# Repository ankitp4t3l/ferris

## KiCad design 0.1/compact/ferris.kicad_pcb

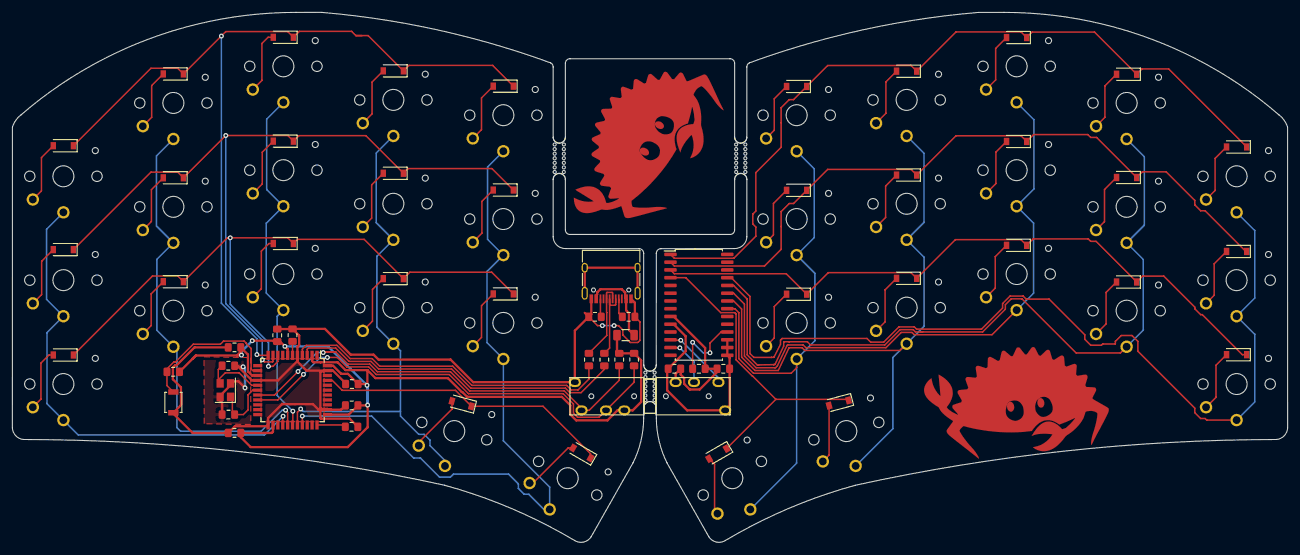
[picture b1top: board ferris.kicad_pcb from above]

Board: 2 copper layers, 208.7 x 86.7 mm, 98 parts (0 on the bottom side), 73 nets.

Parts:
C1, C2: 22p; C_0805_2012Metric_Pad1.15x1.40mm_HandSolder
C3, C4, C5, C6, C9, C10: 0.1u; C_0805_2012Metric_Pad1.15x1.40mm_HandSolder
C7: 4.7u; C_0805_2012Metric_Pad1.15x1.40mm_HandSolder
C8: 1u; C_0805_2012Metric_Pad1.15x1.40mm_HandSolder
D0_0, D0_1, D0_2, D0_3, D0_4, D0_5, D0_6, D0_7, D0_8, D0_9, D1_0, D1_1, D1_2, D1_3, D1_4, D1_5, D1_6, D1_7, D1_8, D1_9, D2_0, D2_1, D2_2, D2_3, D2_4, D2_5, D2_6, D2_7, D2_8, D2_9, D3_3, D3_4, D3_5, D3_6: D; D_SOD-123
F1: 500mA; Fuse_1206_3216Metric
J1: USB C; USB_C_Receptacle_HRO_TYPE-C-31-M-12
Jack0, Jack1: TRRS; TRRS-PJ-320A
K0_0, K0_1, K0_2, K0_3, K0_4, K0_5, K0_6, K0_7, K0_8, K0_9, K1_0, K1_1, K1_2, K1_3, K1_4, K1_5, K1_6, K1_7, K1_8, K1_9, K2_0, K2_1, K2_2, K2_3, K2_4, K2_5, K2_6, K2_7, K2_8, K2_9, K3_3, K3_4, K3_5, K3_6: KEYSW; Choc_PG1350_Choc_Spacing_with_jlcpb_safe_pad_clearance
R1, R2, R9: 10k; R_0805_2012Metric_Pad1.15x1.40mm_HandSolder
R3, R4: 22; R_0805_2012Metric_Pad1.15x1.40mm_HandSolder
R5, R6: 5.1K; R_0805_2012Metric_Pad1.15x1.40mm_HandSolder
R7, R8: 4.7k; R_0805_2012Metric_Pad1.15x1.40mm_HandSolder
SW1: SW_PUSH; SW_SPST_B3U-1000P
U1: ATmega32U4-AU; TQFP-44_10x10mm_P0.8mm
U2: MCP23017_SO; SOIC-28W_7.5x17.9mm_P1.27mm
Y1: Crystal; Crystal_SMD_3225-4Pin_3.2x2.5mm
mouse-bite-5mm-slot, mouse-bite-5mm-slot#2, mouse-bite-5mm-slot#3: VAL**; mouse-bite-5mm-slot

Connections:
+5V: C3.1, C4.1, C5.1, C6.1, C7.1, F1.1, Jack0.R2, R1.2, R7.2, R8.1, U1.2, U1.7, U1.14, U1.24, U1.34, U1.44
/D+: R4.1, U1.4
/D-: R3.1, U1.3
/col0: K0_0.1, K1_0.1, K2_0.1, U1.26
/col1: K0_1.1, K1_1.1, K2_1.1, U1.27
/col2: K0_2.1, K1_2.1, K2_2.1, U1.28
/col3: K0_3.1, K1_3.1, K2_3.1, K3_3.1, U1.29
/col4: K0_4.1, K1_4.1, K2_4.1, K3_4.1, U1.30
/col5: K0_5.1, K1_5.1, K2_5.1, K3_5.1, U2.21
/col6: K0_6.1, K1_6.1, K2_6.1, K3_6.1, U2.22
/col7: K0_7.1, K1_7.1, K2_7.1, U2.23
/col8: K0_8.1, K1_8.1, K2_8.1, U2.24
/col9: K0_9.1, K1_9.1, K2_9.1, U2.25
/row0,0: D0_0.1, D0_1.1, D0_2.1, D0_3.1, D0_4.1, U1.11
/row0,1: D1_0.1, D1_1.1, D1_2.1, D1_3.1, D1_4.1, U1.10
/row0,2: D2_0.1, D2_1.1, D2_2.1, D2_3.1, D2_4.1, U1.9
/row0,3: D3_3.1, D3_4.1, U1.41
/row1,0: D0_5.1, D0_6.1, D0_7.1, D0_8.1, D0_9.1, U2.1
/row1,1: D1_5.1, D1_6.1, D1_7.1, D1_8.1, D1_9.1, U2.2
/row1,2: D2_5.1, D2_6.1, D2_7.1, D2_8.1, D2_9.1, U2.3
/row1,3: D3_5.1, D3_6.1, U2.4
GND: C1.2, C2.1, C3.2, C4.2, C5.2, C6.2, C7.2, C8.2, J1.A1, J1.A12, J1.B1, J1.B12, Jack0.S, R2.1, R5.1, R6.1, SW1.1, U1.5, U1.15, U1.23, U1.35, U1.43, Y1.2, Y1.4
unnamed: C1.1, U1.17, Y1.1
unnamed: C2.2, U1.16, Y1.3
unnamed: C8.1, U1.6
unnamed: D0_0.2, K0_0.2
unnamed: D0_1.2, K0_1.2
unnamed: D0_2.2, K0_2.2
unnamed: D0_3.2, K0_3.2
unnamed: D0_4.2, K0_4.2
unnamed: D0_5.2, K0_5.2
unnamed: D0_6.2, K0_6.2
unnamed: D0_7.2, K0_7.2
unnamed: D0_8.2, K0_8.2
unnamed: D0_9.2, K0_9.2
unnamed: D1_0.2, K1_0.2
unnamed: D1_1.2, K1_1.2
unnamed: D1_2.2, K1_2.2
unnamed: D1_3.2, K1_3.2
unnamed: D1_4.2, K1_4.2
unnamed: D1_5.2, K1_5.2
unnamed: D1_6.2, K1_6.2
unnamed: D1_7.2, K1_7.2
unnamed: D1_8.2, K1_8.2
unnamed: D1_9.2, K1_9.2
unnamed: D2_0.2, K2_0.2
unnamed: D2_1.2, K2_1.2
unnamed: D2_2.2, K2_2.2
unnamed: D2_3.2, K2_3.2
unnamed: D2_4.2, K2_4.2
unnamed: D2_5.2, K2_5.2
unnamed: D2_6.2, K2_6.2
unnamed: D2_7.2, K2_7.2
unnamed: D2_8.2, K2_8.2
unnamed: D2_9.2, K2_9.2
unnamed: D3_3.2, K3_3.2
unnamed: D3_4.2, K3_4.2
unnamed: D3_5.2, K3_5.2
unnamed: D3_6.2, K3_6.2
unnamed: J1.A5, R5.2
unnamed: J1.A6, J1.B6, R4.2
unnamed: J1.A7, J1.B7, R3.2
unnamed: J1.B5, R6.2
unnamed: Jack0.R1, R8.2, U1.19
unnamed: Jack0.T, R7.1, U1.18
unnamed: Jack1.R1, U2.13
unnamed: Jack1.T, U2.12
unnamed: R1.1, SW1.2, U1.13
unnamed: R2.2, U1.33
unnamed: R9.1, U2.18
VCC: F1.2, J1.A4, J1.A9, J1.B4, J1.B9
VDD: C9.2, C10.2, Jack1.R2, R9.2, U2.9
VSS: C9.1, C10.1, Jack1.S, U2.10, U2.15, U2.16, U2.17

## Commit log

2021-09-26 Point footprints submodule to my fork.
2021-09-26 Update submodule ref to point to commit with 5mm tab.
2021-09-26 Make all mouse bites 5mm.
2021-09-27 Make the shebang line compatible with more envs.
    Also add some debugging info to confirm the run-as USER is correct.
2021-09-27 Add JLCPCB order number placeholder.
    Also, make the text on the scrap panel concise.
2021-09-30 Hide all non copper layers.
2021-09-30 Temporarily increase solder mask clearance in order to move traces.
    The solder mask clearance should be set back to 0.05mm after the traces have
    been moved.
2021-09-30 Revert "Temporarily increase solder mask clearance in order to move traces."
    This reverts commit 0fd1c5d82cd2eb1b42baabec2bdd6d8ffa0e2c2a.
2021-09-30 Enable solder mask layers to avoid creating a trace in solder mask clearance.
2021-09-30 Increase pad clearance to 0.7mm.
    Error margins:
    0.2mm NPTH means the hole might be 0.1mm too big around the center.
    0.2mm placement of the hole left or right of where I want it.
    0.254mm is required from NPTH to track
    0.33m is required from PTH to track (we will use this value since it is the greater of NPTH and PTH)
    So, that means, from the edge of the hole to the trace needs to be 0.33mm+0.2mm+0.1mm = 0.63mm
2021-09-30 Modify the switch footprint to add pad clearance.
2021-10-03 Sync fp submodule.
2021-10-03 Move traces around the jlcpcb clearance switch pads.
